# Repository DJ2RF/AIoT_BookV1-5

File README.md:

ESP32 / ESP-IDF reference projects from the AIoT Workshop book series covering IoT nodes, MQTT communication, OTA updates and energy-efficient embedded design.

## Weitere Tipps zu den Sourcen und zur Installation im Buch

# 📘 AIoT-Werkstatt – Band 1

https://www.amazon.de/dp/B0GN1FHHRY

Hardware- und IoT-Grundlagen mit ESP32, MQTT und OTA

Nerd-Verlag 

https://nerdverlag.com

Video AIoT Book Volume1 Video Volume1 https://www.youtube.com/watch?v=RnY7Kfq0jc0

Video AIoT Book Volume1 Video Volume2 https://www.youtube.com/watch?v=WDLXiZMIw_Q

Video AIoT Book Volume1 Video Volume3 https://www.youtube.com/watch?v=AJKTUtD__mQ

## English at buttom

# AIoT_BookV1-5
## AIoT Werkstatt – Buchprojekt Band 1–5

https://nerdverlag.com

(c) 2026 Friedrich Riedhammer DJ2RF

Willkommen zum **AIoT Werkstatt Projekt** – einer praxisorientierten Entwicklungsreihe rund um  
**Artificial Intelligence of Things (AIoT)**, Embedded-Systeme, Funktechnik und Hardwareentwicklung.

Dieses Repository enthält die vollständigen Entwicklungsdaten zu den Buchbänden:

- Hardware-Designs (KiCad)
- Fertigungsdaten (Gerber, BOM, Pick & Place)
- Konstruktion Stencil (3D)
- Firmware-Projekte
- Beispielsoftware
- Abbildungen und Begleitmaterialien zu den Büchern
- Video-Begleitserien

# Inhalt der Buchreihe

## Band 1 – Grundlagen & Hardwaredesign
- Elektronik-Grundlagen
- Schaltplanentwicklung
- PCB-Layout mit KiCad
- Fertigungsprozesse und Bestückung

## Band 2 – Embedded Firmware
- Mikrocontroller-Programmierung
- ESP32-Plattform
- Kommunikationsschnittstellen
- Low-Power-Design

## Band 3 – Funk & SDR
- RF-Grundlagen
- SDR-Systeme
- IoT-Funkprotokolle
- Antennenpraxis

## Band 4 – AIoT Systeme
- Edge-AI
- Sensordatenverarbeitung
- Embedded Machine Learning
- Sehen, Hören, Entscheiden

## Band 5 – Praxisprojekte
- Komplettprojekte von der Idee bis zum Produkt
- Robotik
- Feldtests
- Produktionsvorbereitung

## Haftungsausschluss / Disclaimer

Die in diesem Repository bereitgestellten Inhalte, einschließlich Hardware-Designs, Schaltpläne, Layouts, Fertigungsdaten, Firmware, Software, Dokumentation und sonstiger Materialien, werden ohne jegliche ausdrückliche oder stillschweigende Gewährleistung bereitgestellt.

Der Autor übernimmt insbesondere keine Gewähr für:

- die Funktionsfähigkeit oder Fehlerfreiheit der bereitgestellten Designs und Software
- die Eignung für einen bestimmten Zweck
- Schäden an Geräten, Bauteilen oder Systemen
- direkte oder indirekte Schäden, Folgeschäden oder wirtschaftliche Verluste, die durch die Nutzung der bereitgestellten Informationen entstehen

Die Nutzung der bereitgestellten Unterlagen erfolgt vollständig auf eigenes Risiko.

Alle Anwender sind selbst dafür verantwortlich, Designs, Schaltungen, Software und Fertigungsdaten vor praktischer Anwendung sorgfältig zu prüfen, zu validieren und unter sicheren Bedingungen zu testen.

Dieses Repository stellt kein zertifiziertes Referenzdesign, kein fertiges Produkt und keine sicherheitsgeprüfte Entwicklungsbasis dar.

# English

# AIoT_BookV1-5
## AIoT Workshop – Book Project Volumes 1–5

https://nerdverlag.com

(c) 2026 Friedrich Riedhammer DJ2RF

Welcome to the **AIoT Workshop Project** – a practice-oriented development series focused on  
**Artificial Intelligence of Things (AIoT)**, embedded systems, RF technology, and hardware design.

This repository contains the complete development data for the book series:

- Hardware designs (KiCad)
- Manufacturing data (Gerber, BOM, Pick & Place)
- Stencil construction (3D)
- Firmware projects
- Example software
- Figures and supplementary book materials
- Companion video series

# Book Series Contents

## Volume 1 – Fundamentals & Hardware Design
- Electronics fundamentals
- Schematic design
- PCB layout with KiCad
- Manufacturing processes and assembly

## Volume 2 – Embedded Firmware
- Microcontroller programming
- ESP32 platform
- Communication interfaces
- Low-power design

## Volume 3 – RF & SDR
- RF fundamentals
- SDR systems
- IoT radio protocols
- Antenna practice

## Volume 4 – AIoT Systems
- Edge AI
- Sensor data processing
- Embedded machine learning
- Seeing, hearing, deciding

## Volume 5 – Practical Projects
- Complete projects from idea to product
- Robotics
- Field testing
- Production preparation

## Disclaimer / Warranty Exclusion

All materials provided in this repository, including hardware designs, schematics, PCB layouts, manufacturing files, firmware, software, documentation, and any related content, are provided **“as is”** without any express or implied warranty.

The author specifically disclaims any warranties regarding:

- functionality, performance, or error-free operation of the provided designs and software
- fitness for a particular purpose
- damage to devices, components, or systems
- any direct, indirect, incidental, consequential, or economic damages resulting from the use of the provided information

Use of the provided materials is entirely at the user's own risk.

Users are solely responsible for verifying, validating, and testing all designs, circuits, software, and manufacturing data before practical use and for ensuring safe operating conditions.

This repository does not constitute a certified reference design, finished product, or safety-approved development platform.

## Keywords
esp32
esp-idf
iot
aiot
embedded-systems
mqtt
ota-update
firmware
deep-sleep
hardware-design
pcb
internet-of-things

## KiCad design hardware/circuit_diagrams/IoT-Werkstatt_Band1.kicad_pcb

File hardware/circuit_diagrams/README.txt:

IoT-Werkstatt – KiCad 9.0.6 Schaltplan-Skeleton (clean)
- Optimized text placement for KiCad 9.x
- Minimal annotations to avoid label drift
- Hierarchical sheets ready for expansion

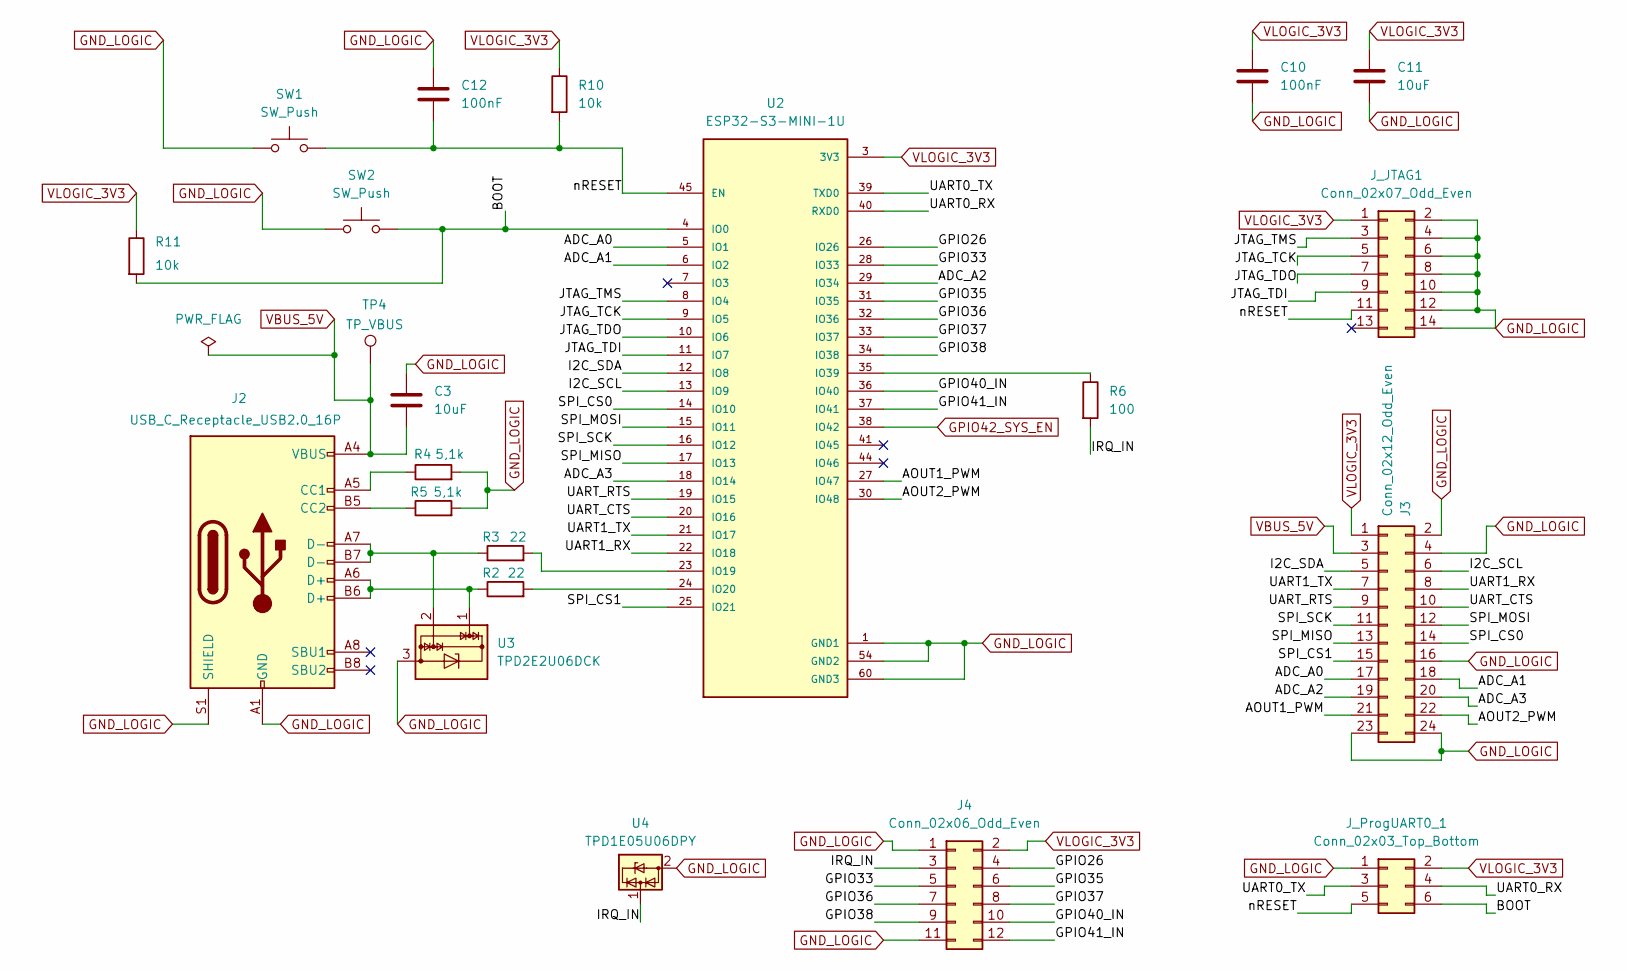
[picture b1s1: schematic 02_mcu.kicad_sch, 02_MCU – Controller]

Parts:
C3, C11: 10uF; C_0805_2012Metric
C10, C12: 100nF; C_0603_1608Metric
J2: USB_C_Receptacle_USB2.0_16P; USB_C_Receptacle_Amphenol_124019772112A
J3: Conn_02x12_Odd_Even; PinHeader_2x12_P2.54mm_Vertical
J4: Conn_02x06_Odd_Even; PinHeader_2x06_P2.54mm_Vertical
J_JTAG1: Conn_02x07_Odd_Even; IDC-Header_2x07_P2.54mm_Vertical
J_ProgUART0_1: Conn_02x03_Top_Bottom; IDC-Header_2x03_P2.54mm_Vertical
R2, R3: 22; R_0603_1608Metric
R4, R5: 5,1k; R_0603_1608Metric
R6: 100; R_0603_1608Metric
R10, R11: 10k; R_0603_1608Metric
SW1, SW2: SW_Push; SW_SPST_TL3342
TP4: TP_VBUS; TestPoint_Pad_D1.0mm
U2: ESP32-S3-MINI-1U; XCVR_ESP32-S3-MINI-1U-N8; PARTREV 1.2
U3: TPD2E2U06DCK; SOT-323_SC-70
U4: TPD1E05U06DPY; Texas_DPY0002A_0.6x1mm_P0.65mm

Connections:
/02_MCU/ADC_A0: J3.17, U2.5 (IO1)
/02_MCU/ADC_A1: J3.18, U2.6 (IO2)
/02_MCU/ADC_A2: J3.19, U2.29 (IO34)
/02_MCU/ADC_A3: J3.20, U2.18 (IO14)
/02_MCU/AOUT1_PWM: J3.21, U2.27 (IO47)
/02_MCU/AOUT2_PWM: J3.22, U2.30 (IO48)
/02_MCU/BOOT: J_ProgUART0_1.6, R11.2, SW2.2, U2.4 (IO0)
/02_MCU/GPIO26: J4.4, U2.26 (IO26)
/02_MCU/GPIO33: J4.5, U2.28 (IO33)
/02_MCU/GPIO35: J4.6, U2.31 (IO35)
/02_MCU/GPIO36: J4.7, U2.32 (IO36)
/02_MCU/GPIO37: J4.8, U2.33 (IO37)
/02_MCU/GPIO38: J4.9, U2.34 (IO38)
/02_MCU/GPIO40_IN: J4.10, U2.36 (IO40)
/02_MCU/GPIO41_IN: J4.12, U2.37 (IO41)
/02_MCU/I2C_SCL: J3.6, U2.13 (IO9)
/02_MCU/I2C_SDA: J3.5, U2.12 (IO8)
/02_MCU/IRQ_IN: J4.3, R6.2, U4.1 (I/O)
/02_MCU/JTAG_TCK: J_JTAG1.5, U2.9 (IO5)
/02_MCU/JTAG_TDI: J_JTAG1.9, U2.11 (IO7)
/02_MCU/JTAG_TDO: J_JTAG1.7, U2.10 (IO6)
/02_MCU/JTAG_TMS: J_JTAG1.3, U2.8 (IO4)
/02_MCU/SPI_CS0: J3.14, U2.14 (IO10)
/02_MCU/SPI_CS1: J3.15, U2.25 (IO21)
/02_MCU/SPI_MISO: J3.13, U2.17 (IO13)
/02_MCU/SPI_MOSI: J3.12, U2.15 (IO11)
/02_MCU/SPI_SCK: J3.11, U2.16 (IO12)
/02_MCU/UART0_RX: J_ProgUART0_1.4, U2.40 (RXD0)
/02_MCU/UART0_TX: J_ProgUART0_1.3, U2.39 (TXD0)
/02_MCU/UART1_RX: J3.8, U2.22 (IO18)
/02_MCU/UART1_TX: J3.7, U2.21 (IO17)
/02_MCU/UART_CTS: J3.10, U2.20 (IO16)
/02_MCU/UART_RTS: J3.9, U2.19 (IO15)
/02_MCU/nRESET: C12.2, J_JTAG1.11, J_ProgUART0_1.5, R10.2, SW1.2, U2.45 (EN)
GND_LOGIC: C3.1, C10.2, C11.2, C12.1, J2.A1 (GND), J2.A12 (GND), J2.B1 (GND), J2.B12 (GND), J2.S1 (SHIELD), J3.2, J3.4, J3.16, J3.23, J3.24, J4.1, J4.11, J_JTAG1.2, J_JTAG1.4, J_JTAG1.6, J_JTAG1.8, J_JTAG1.10, J_JTAG1.12, J_JTAG1.14, J_ProgUART0_1.1, R4.2, R5.2, SW1.1, SW2.1, U2.1 (GND1), U2.2 (GND1), U2.42 (GND1), U2.43 (GND1), U2.46 (GND1), U2.47 (GND1), U2.48 (GND1), U2.49 (GND1), U2.50 (GND1), U2.51 (GND1), U2.52 (GND1), U2.53 (GND1), U2.54 (GND2), U2.55 (GND2), U2.56 (GND2), U2.57 (GND2), U2.58 (GND2), U2.59 (GND2), U2.60 (GND3), U2.61_1 (GND3), U2.61_2 (GND3), U2.61_3 (GND3), U2.61_4 (GND3), U2.61_5 (GND3), U2.61_6 (GND3), U2.61_7 (GND3), U2.61_8 (GND3), U2.61_9 (GND3), U2.62 (GND2), U2.63 (GND2), U2.64 (GND2), U2.65 (GND2), U3.3, U4.2 (GND); also elsewhere on the board
GPIO42_SYS_EN: U2.38 (IO42); also elsewhere on the board
unnamed: J2.A5 (CC1), R4.1
unnamed: J2.B5 (CC2), R5.1
unnamed: J2.A6 (D+), J2.B6 (D+), R2.1, U3.1
unnamed: J2.A7 (D-), J2.B7 (D-), R3.1, U3.2
unnamed: R3.2, U2.23 (IO19)
unnamed: R2.2, U2.24 (IO20)
unnamed: R6.1, U2.35 (IO39)
VBUS_5V: C3.2, J2.A4 (VBUS), J2.A9 (VBUS), J2.B4 (VBUS), J2.B9 (VBUS), J3.3, TP4.1; also elsewhere on the board
VLOGIC_3V3: C10.1, C11.1, J3.1, J4.2, J_JTAG1.1, J_ProgUART0_1.2, R10.1, R11.1, U2.3 (3V3); also elsewhere on the board

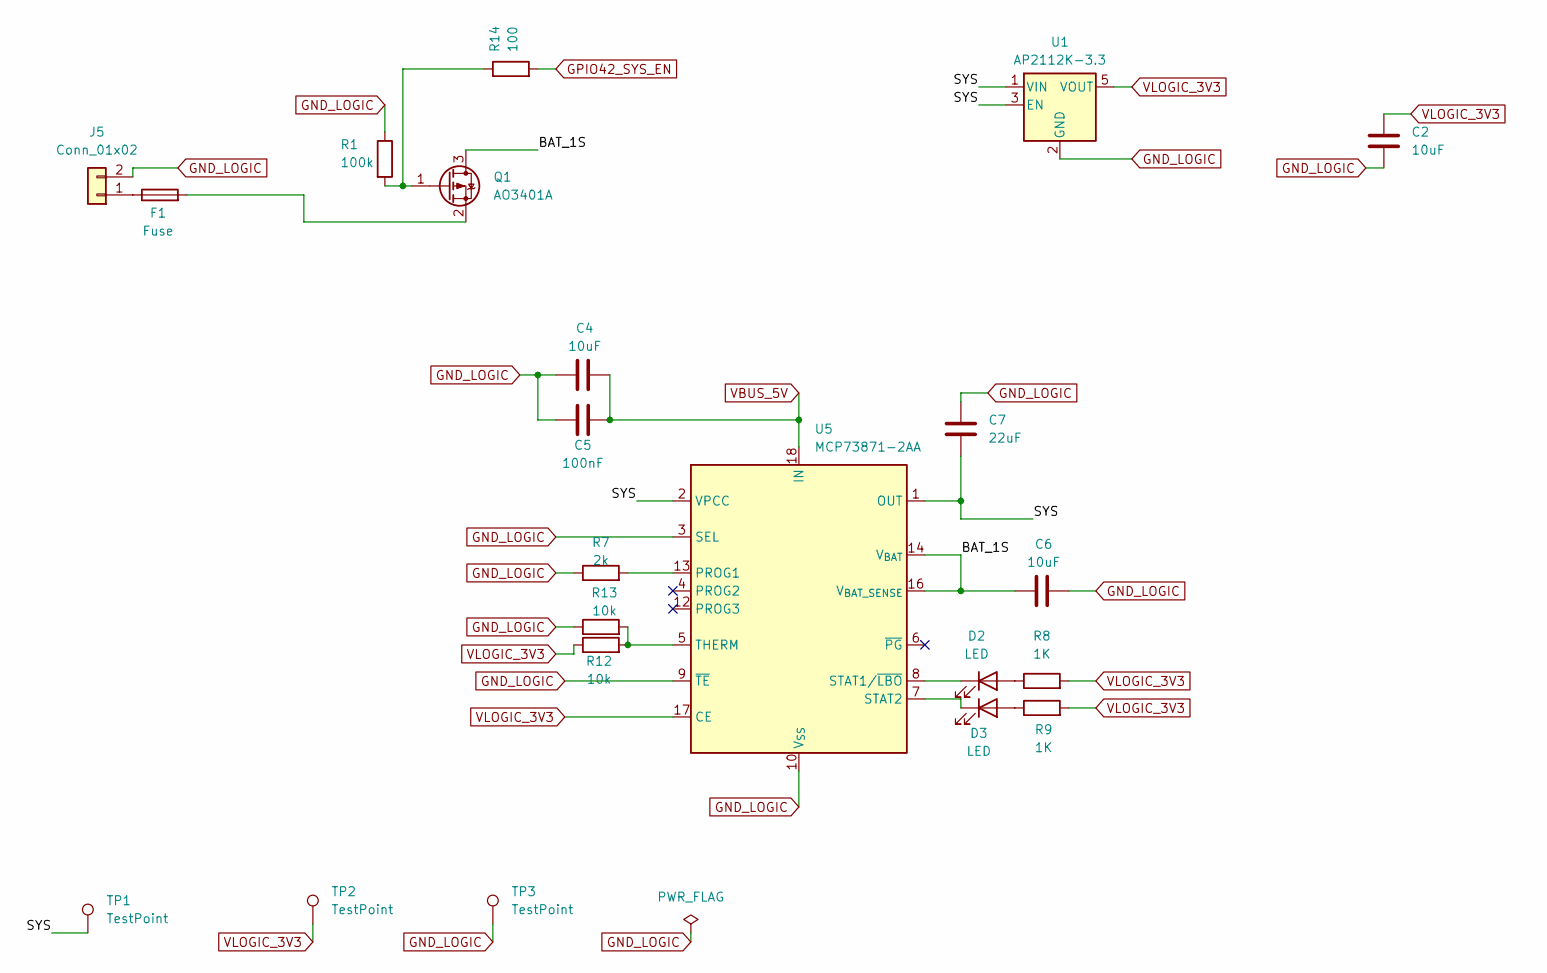
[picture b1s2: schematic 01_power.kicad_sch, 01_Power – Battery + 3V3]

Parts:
C2, C4, C6: 10uF; C_0805_2012Metric
C5: 100nF; C_0603_1608Metric
C7: 22uF; C_0805_2012Metric
D2, D3: LED; LED_0603_1608Metric
F1: Fuse; Fuse_1206_3216Metric
J5: Conn_01x02; Molex_CLIK-Mate_502386-0270_1x02-1MP_P1.25mm_Horizontal
Q1: AO3401A; SOT-23
R1: 100k; R_0603_1608Metric
R7: 2k; R_0603_1608Metric
R8, R9: 1K; R_0603_1608Metric
R12, R13: 10k; R_0603_1608Metric
R14: 100; R_0603_1608Metric
TP1, TP2, TP3: TestPoint; TestPoint_Pad_D1.0mm
U1: AP2112K-3.3; SOT-23-5
U5: MCP73871-2AA; QFN-20-1EP_4x4mm_P0.5mm_EP2.5x2.5mm

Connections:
/01_Power/BAT_1S: C6.1, Q1.3 (D), U5.14 (V_{BAT}), U5.15 (V_{BAT}), U5.16 (V_{BAT_SENSE})
/01_Power/SYS: C7.2, TP1.1, U1.1 (VIN), U1.3 (EN), U5.1 (OUT), U5.2 (VPCC), U5.20 (OUT)
GND_LOGIC: C2.2, C4.1, C5.2, C6.2, C7.1, J5.2, R1.1, R7.1, R13.1, TP3.1, U1.2 (GND), U5.3 (SEL), U5.9 (~TE), U5.10 (V_{SS}), U5.11 (V_{SS}), U5.21 (V_{SS}); also elsewhere on the board
GPIO42_SYS_EN: R14.2; also elsewhere on the board
unnamed: D2.2 (A), R8.1
unnamed: D2.1 (K), U5.8 (STAT1/~LBO)
unnamed: D3.2 (A), R9.1
unnamed: D3.1 (K), U5.7 (STAT2)
unnamed: F1.1, J5.1
unnamed: Q1.1 (G), R1.2, R14.1
unnamed: F1.2, Q1.2 (S)
unnamed: R7.2, U5.13 (PROG1)
unnamed: R12.2, R13.2, U5.5 (THERM)
VBUS_5V: C4.2, C5.1, U5.18 (IN), U5.19 (IN); also elsewhere on the board
VLOGIC_3V3: C2.1, R8.2, R9.2, R12.1, TP2.1, U1.5 (VOUT), U5.17 (CE); also elsewhere on the board

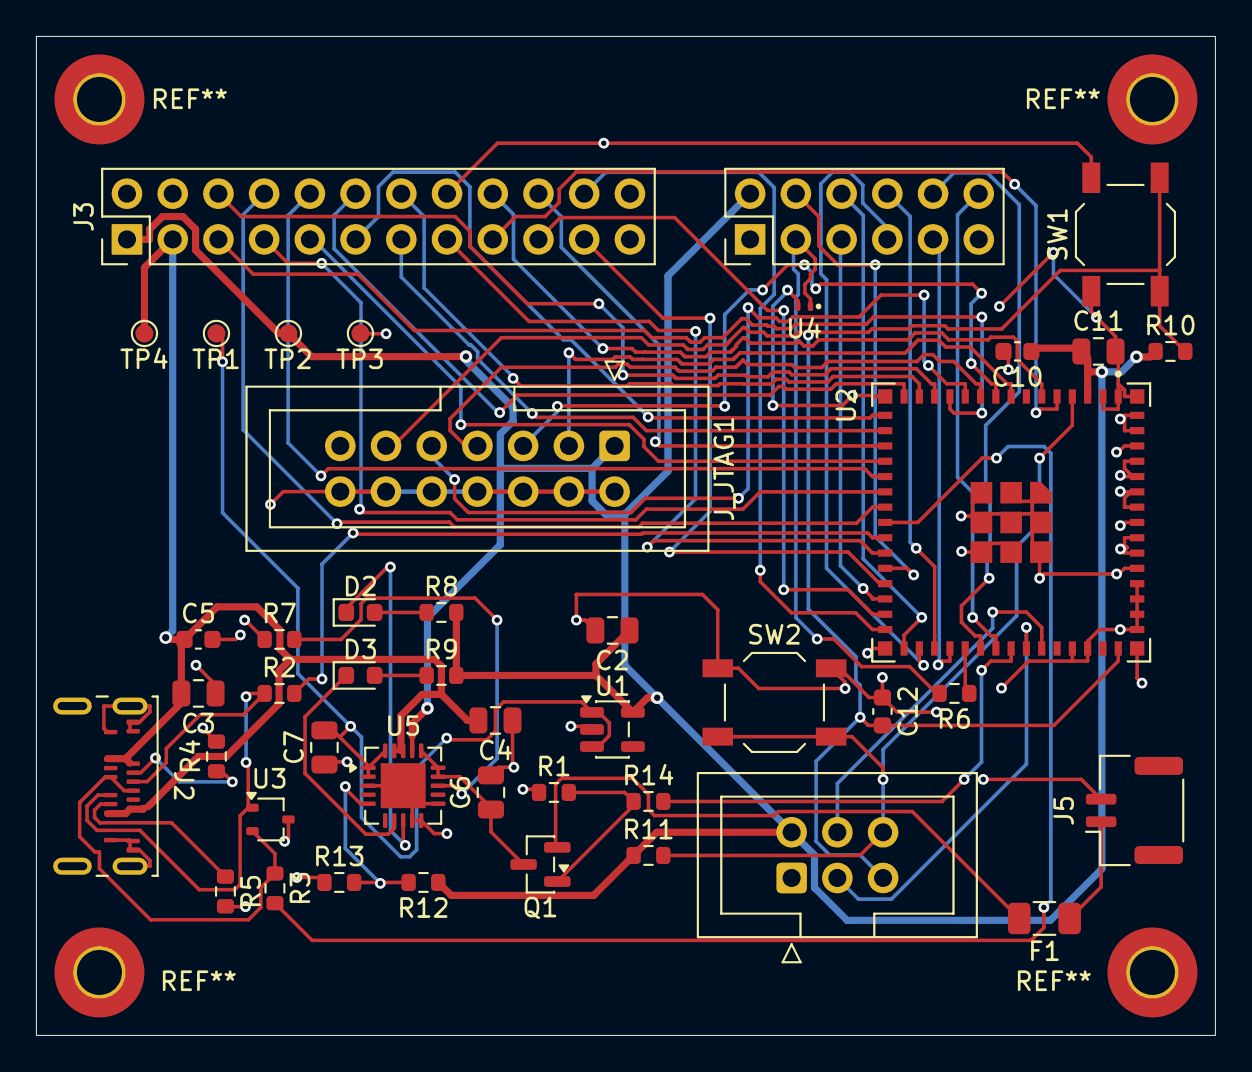
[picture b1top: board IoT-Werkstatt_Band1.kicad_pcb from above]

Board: 2 copper layers, 65.5 x 55.5 mm, 44 parts (0 on the bottom side), 56 nets.

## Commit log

2026-02-08 Fix typos in README.md for video links
2026-02-08 Update video link from Volume2 to Volume3
2026-02-08 What it is
2026-02-09 Disclaimer added
2026-02-10 Added GPIO_Test
2026-02-10 Add AIot GPIO Input
2026-02-10 Added AIoT_I2C_Test
2026-02-10 Added_Real_I2C_Sensor
2026-02-10 Added ADC Test
2026-02-10 Added Copyright
2026-02-10 Added PW_and_Energy
2026-02-10 Added AIoT First_WLAN
2026-02-10 AIoT_First_WLAN_Doku
2026-02-10 added MQTT
2026-02-10 Added OTA
2026-02-11 Added Final Node
2026-02-11 Added Final Node Prof
2026-02-11 Update README with installation tips and book link
    Added additional tips for sources and installation.
2026-02-12 Change Amazon link for AIoT-Werkstatt
    Updated the Amazon link in the README.
2026-02-13 Update README with YouTube video links
    Added links to YouTube videos related to AIoT Book Volume 1.
2026-03-05 Add keywords section to README
    Added keywords section for better project discoverability.
2026-03-05 Add keywords to README for better discoverability
    Added keywords related to ESP32 and IoT.
2026-03-05 Clean up keywords section in README.md
    Removed extra line breaks from the keywords section.

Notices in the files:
hardware/circuit_diagrams/01_power.kicad_sch:
Nerd-Verlag F. Riedhammer (c) 2026
hardware/circuit_diagrams/IoT-Werkstatt_Band1.kicad_pcb:
ESP32 AIot Project Nerd-Verlag (c) 2026 fritz@nerdverlag.com
